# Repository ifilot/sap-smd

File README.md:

# Modular 8-bit "Simple as Possible" TTL-Logics Computer

This project showcases the design and construction of a modular 8-bit computer
built with TTL logic units. The core principle behind the project is to create a
**"Simple as Possible"** system, focusing on simplicity, modularity, and
compactness.

## Key Features

- **TTL Logic-Based Design**: The computer is built using traditional TTL
  (Transistor-Transistor Logic) components, adhering to a fundamental, hands-on
  approach to computing.
- **Modular Architecture**: Designed for modularity, each functional unit (ALU,
  registers, memory, control logic, etc.) is implemented as a separate module,
  allowing for easy debugging, customization, and scalability.
- **Compact Form Factor**: By predominantly using **SMD (Surface-Mount Device)**
  components, the overall size of the computer is significantly reduced compared
  to traditional through-hole designs, making it more efficient and portable.
- **Educational Value**: Serves as an excellent learning resource for
  understanding the basic principles of digital logic, computer architecture,
  and how these concepts come together to form a functional computing system.
- **Customization Potential**: The modular approach allows users to experiment
  with different configurations and expand the system to suit specific needs or
  projects.

## Technical specifications

- 8 bit program counter
- 256 bytes of RAM and 256 bytes of program ROM
- 256 configurable programs via a dip switch
- Three general-purpose register: A, B and T
- Simple ALU allowing for addition and subtraction
- EEPROM-configurable instruction decoder
- Custom assembly language including Python-based assembler

## Goals of the Project

The project aims to:
1. **Simplify Complexity**: Break down the workings of a computer into
   comprehensible modules without unnecessary abstraction.
2. **Promote Learning**: Provide an accessible platform for enthusiasts,
   educators, and students to explore computer design.
3. **Encourage Miniaturization**: Demonstrate how SMD components can be used
   effectively in hobbyist and educational projects to save space while
   maintaining functionality.

## Why SMD Components?

SMD components offer several advantages:
- **Space Efficiency**: Significantly smaller than through-hole components,
  enabling more compact designs.
- **Modern Availability**: Easier to source and more reflective of contemporary
  electronics practices.
- **Scalability**: Allows for a more complex system without requiring excessive
  physical space.

## Who Is This For?

This project is ideal for:
- **Hobbyists and Makers** interested in retrocomputing and hardware design.
- **Students and Educators** looking for hands-on experience with digital logic
  and computing fundamentals.
- **Researchers and Enthusiasts** exploring minimalist computing and modular
  design approaches.

## Getting Started

1. **Clone the Repository**: Download the files and schematics from this
   repository.
2. **Review the Documentation**: Detailed explanations and schematics for each
   module are available in the `docs` directory.
3. **Assemble and Test**: Follow the provided instructions to assemble and test
   the modules step-by-step.
4. **Customize**: Modify or expand the design to suit your needs or explore
   specific areas of interest.

## Contributing

Contributions to this project are welcome! If you have ideas for improvements,
additional features, or alternative designs, feel free to fork the repository
and submit a pull request.

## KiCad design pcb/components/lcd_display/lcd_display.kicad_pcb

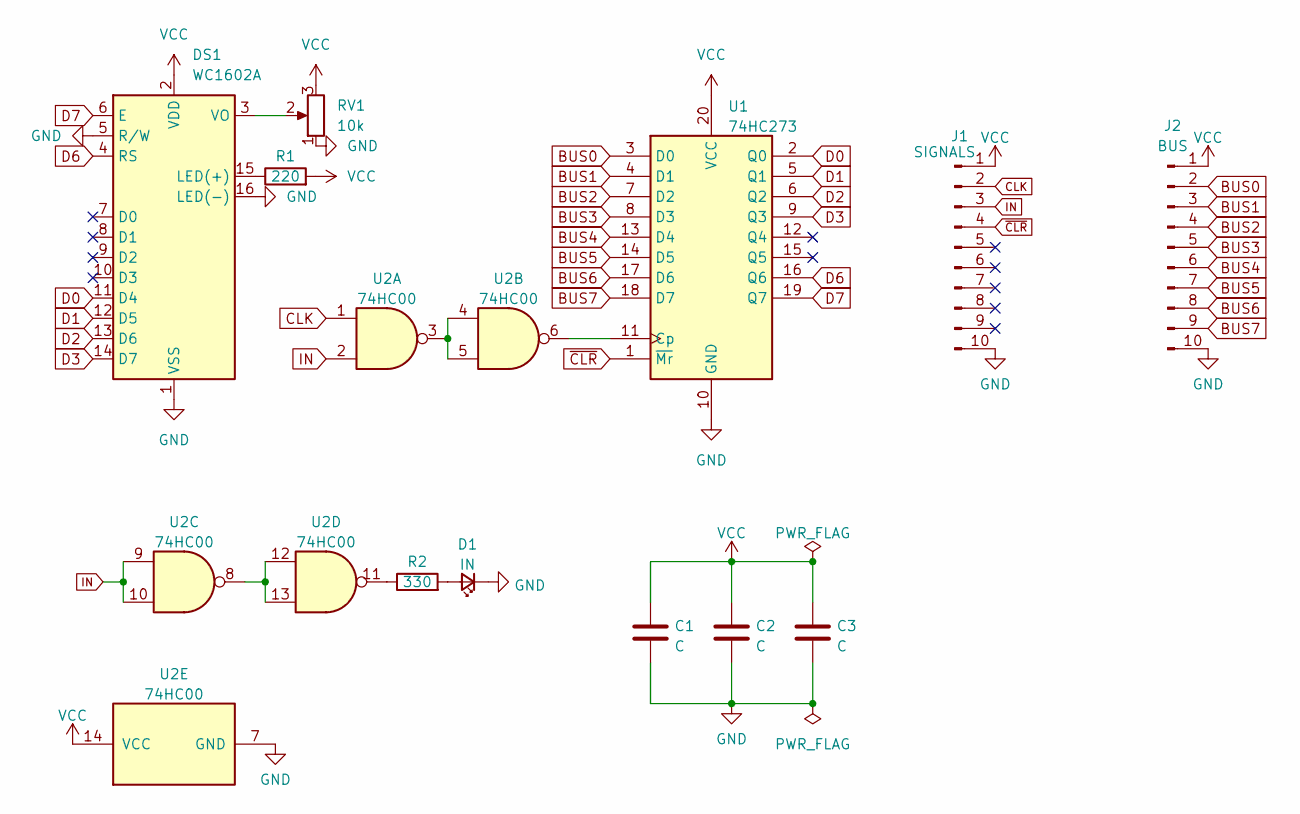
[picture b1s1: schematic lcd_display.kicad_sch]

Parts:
C1, C2, C3: C; C_0805_2012Metric
D1: IN; LED_0805_2012Metric
DS1: WC1602A
J1: SIGNALS; PinHeader_1x10_P2.54mm_Vertical
J2: BUS; PinHeader_1x10_P2.54mm_Vertical
R1: 220; R_0805_2012Metric
R2: 330; R_0805_2012Metric
RV1: 10k; Potentiometer_Bourns_3296W_Vertical
U1: 74HC273; SOIC-20W_7.5x12.8mm_P1.27mm
U2: 74HC00; SO-14_3.9x8.65mm_P1.27mm

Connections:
BUS0: J2.2, U1.3 (D0)
BUS1: J2.3, U1.4 (D1)
BUS2: J2.4, U1.7 (D2)
BUS3: J2.5, U1.8 (D3)
BUS4: J2.6, U1.13 (D4)
BUS5: J2.7, U1.14 (D5)
BUS6: J2.8, U1.17 (D6)
BUS7: J2.9, U1.18 (D7)
CLK: J1.2, U2.1
D0: DS1.11 (D4), U1.2 (Q0)
D1: DS1.12 (D5), U1.5 (Q1)
D2: DS1.13 (D6), U1.6 (Q2)
D3: DS1.14 (D7), U1.9 (Q3)
D6: DS1.4 (RS), U1.16 (Q6)
D7: DS1.6 (E), U1.19 (Q7)
GND: C1.2, C2.2, C3.2, D1.1 (K), DS1.1 (VSS), DS1.5 (R/W), DS1.16 (LED(-)), J1.10, J2.10, RV1.1, U1.10 (GND), U2.7 (GND)
IN: J1.3, U2.2, U2.9, U2.10
unnamed: D1.2 (A), R2.2
unnamed: DS1.15 (LED(+)), R1.1
unnamed: DS1.3 (VO), RV1.2
unnamed: R2.1, U2.11
unnamed: U1.11 (Cp), U2.6
unnamed: U2.3, U2.4, U2.5
unnamed: U2.8, U2.12, U2.13
VCC: C1.1, C2.1, C3.1, DS1.2 (VDD), J1.1, J2.1, R1.2, RV1.3, U1.20 (VCC), U2.14 (VCC)
~CLR: J1.4, U1.1 (~Mr)

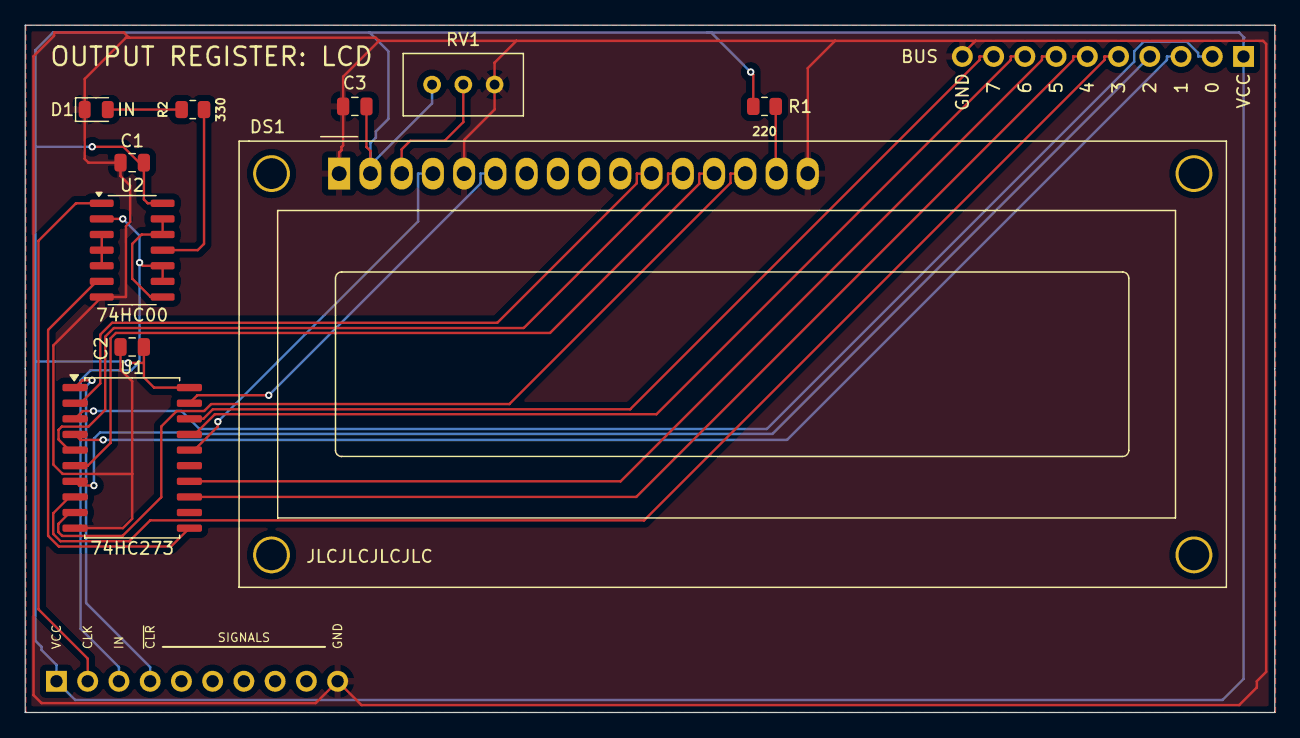
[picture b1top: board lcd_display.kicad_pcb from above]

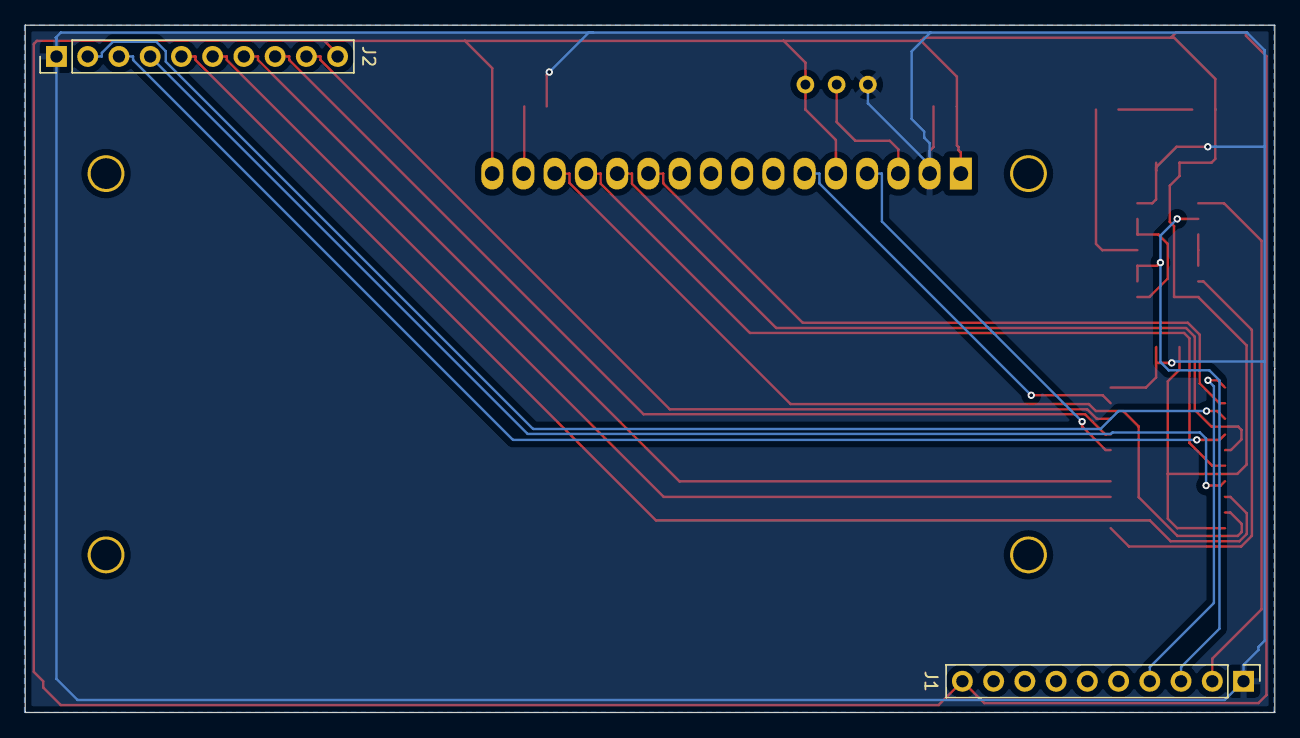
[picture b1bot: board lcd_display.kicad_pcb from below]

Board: 2 copper layers, 101.6 x 55.9 mm, 12 parts (2 on the bottom side), 26 nets.

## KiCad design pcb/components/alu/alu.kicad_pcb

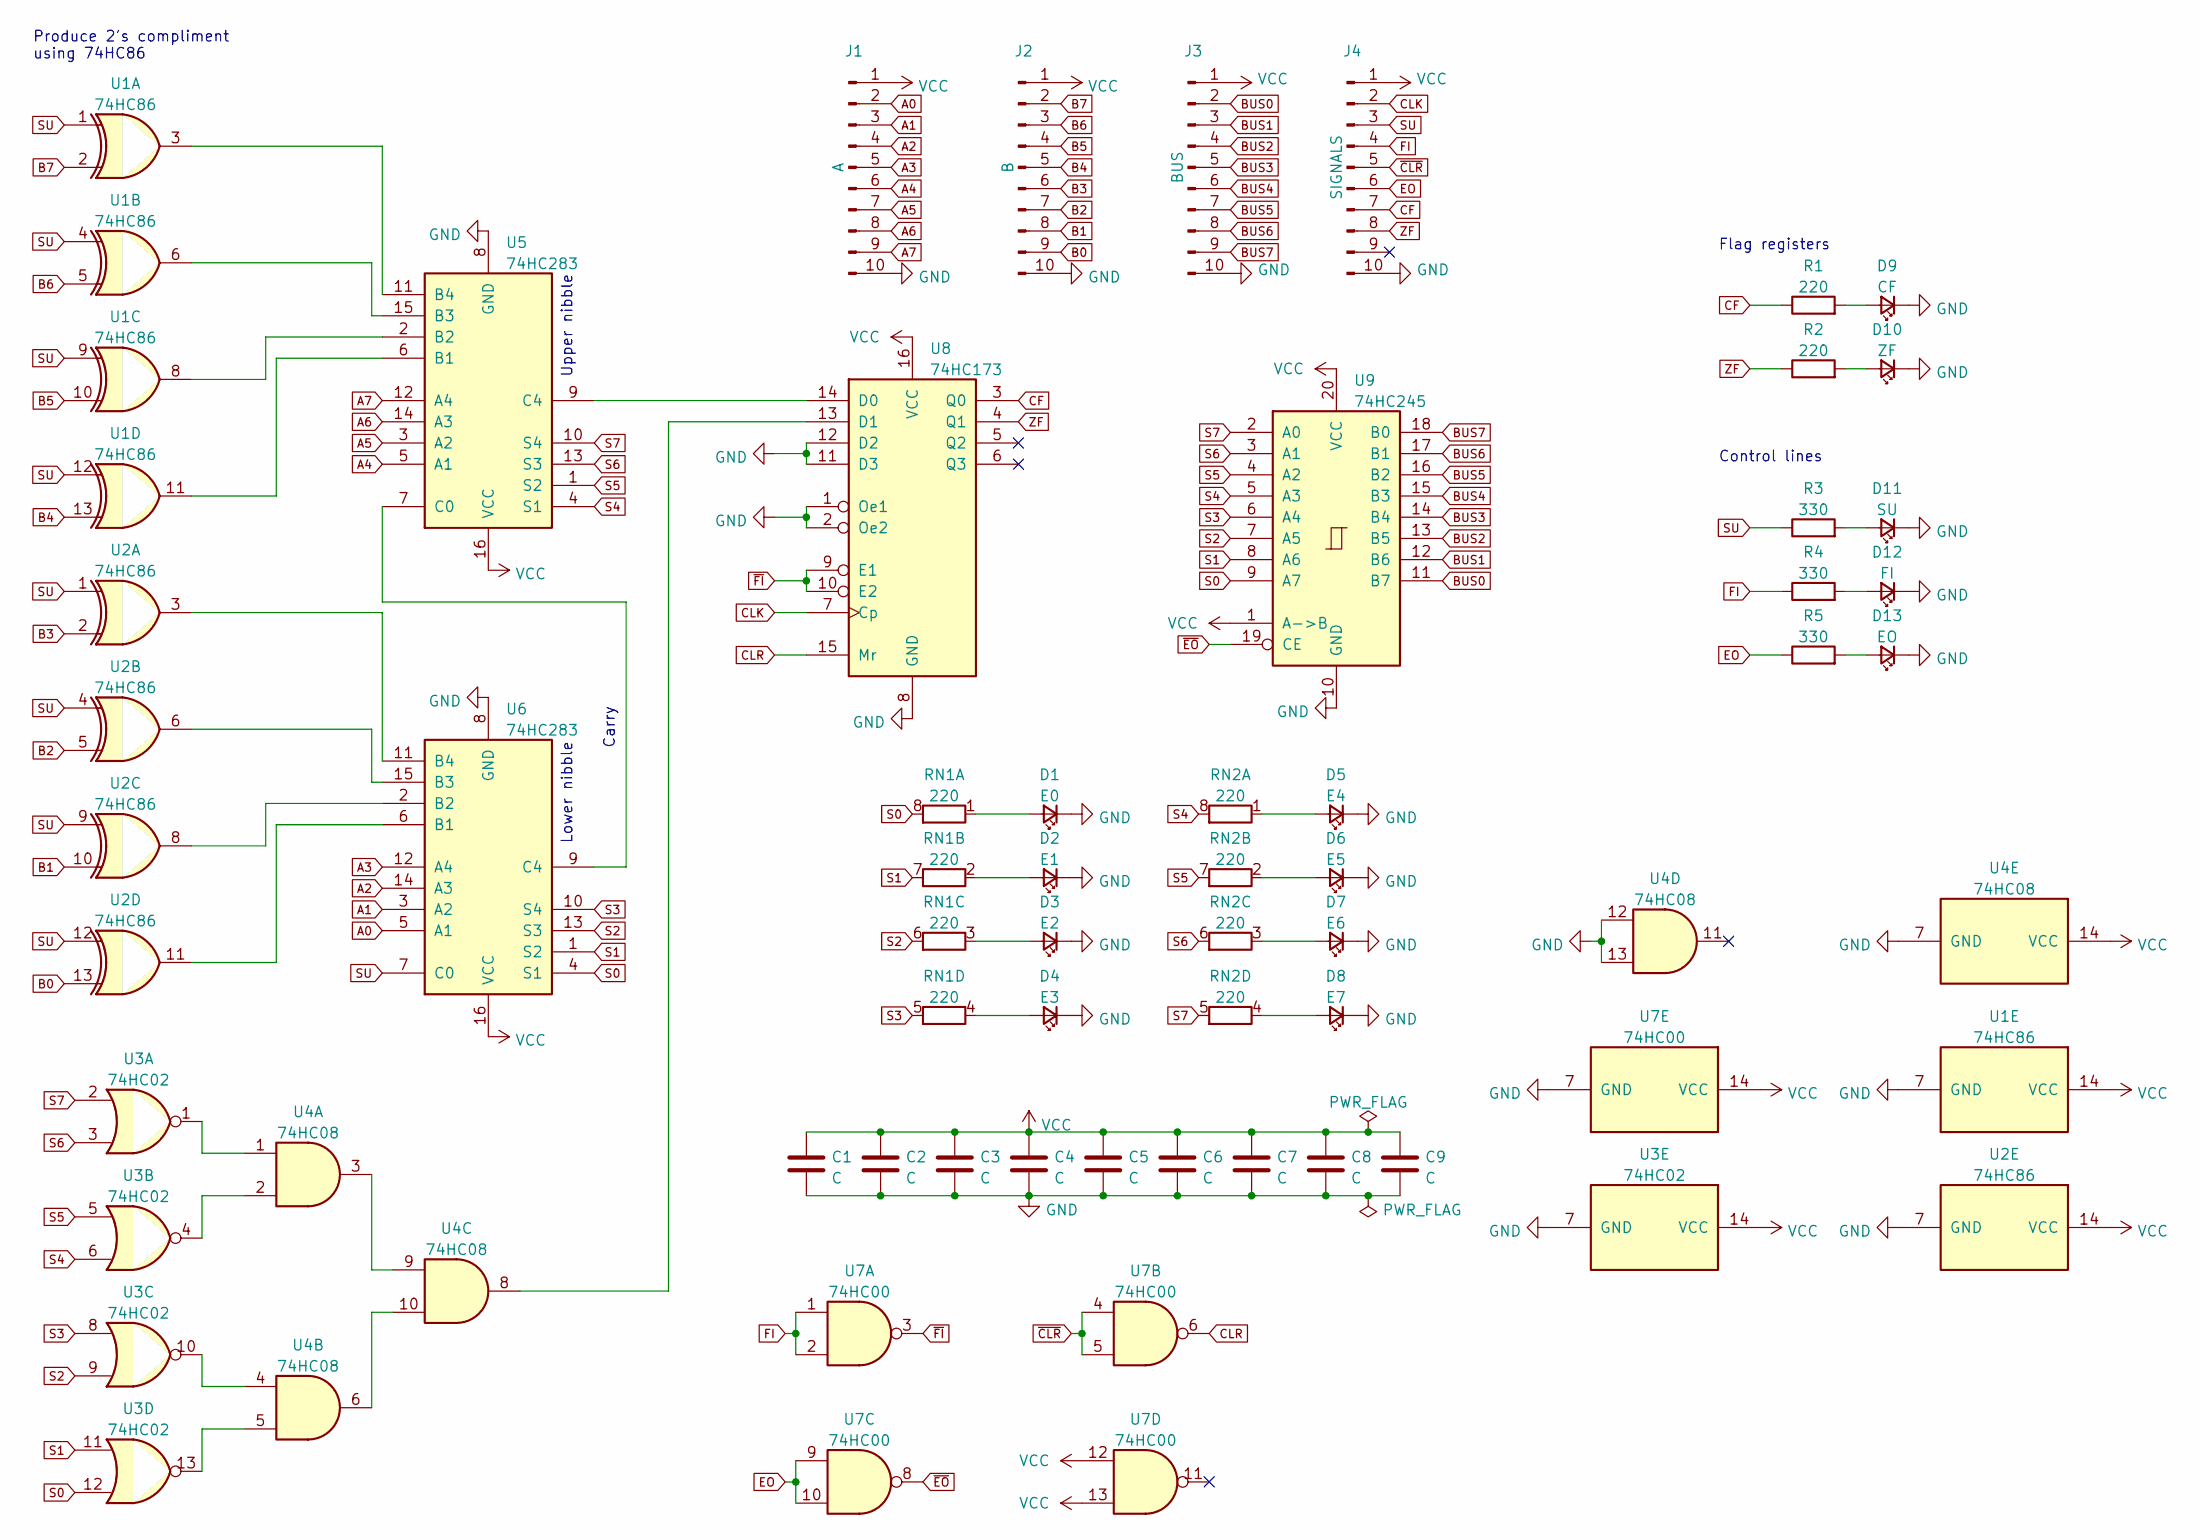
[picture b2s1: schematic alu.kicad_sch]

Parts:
C1, C2, C3, C4, C5, C6, C7, C8, C9: C; C_0805_2012Metric
D1: E0; LED_0805_2012Metric
D2: E1; LED_0805_2012Metric
D3: E2; LED_0805_2012Metric
D4: E3; LED_0805_2012Metric
D5: E4; LED_0805_2012Metric
D6: E5; LED_0805_2012Metric
D7: E6; LED_0805_2012Metric
D8: E7; LED_0805_2012Metric
D9: CF; LED_0805_2012Metric
D10: ZF; LED_0805_2012Metric
D11: SU; LED_0805_2012Metric
D12: FI; LED_0805_2012Metric
D13: EO; LED_0805_2012Metric
J1: A; PinHeader_1x10_P2.54mm_Vertical
J2: B; PinHeader_1x10_P2.54mm_Vertical
J3: BUS; PinHeader_1x10_P2.54mm_Vertical
J4: SIGNALS; PinHeader_1x10_P2.54mm_Vertical
R1, R2: 220; R_0805_2012Metric
R3, R4, R5: 330; R_0805_2012Metric
RN1, RN2: 220; R_Array_Convex_4x0603
U1, U2: 74HC86; SO-14_3.9x8.65mm_P1.27mm
U3: 74HC02; SO-14_3.9x8.65mm_P1.27mm
U4: 74HC08; SO-14_3.9x8.65mm_P1.27mm
U5, U6: 74HC283; SO-16_3.9x9.9mm_P1.27mm
U7: 74HC00; SO-14_3.9x8.65mm_P1.27mm
U8: 74HC173; SO-16_3.9x9.9mm_P1.27mm
U9: 74HC245; SO-20_12.8x7.5mm_P1.27mm

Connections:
A0: J1.2, U6.5 (A1)
A1: J1.3, U6.3 (A2)
A2: J1.4, U6.14 (A3)
A3: J1.5, U6.12 (A4)
A4: J1.6, U5.5 (A1)
A5: J1.7, U5.3 (A2)
A6: J1.8, U5.14 (A3)
A7: J1.9, U5.12 (A4)
B0: J2.9, U2.13
B1: J2.8, U2.10
B2: J2.7, U2.5
B3: J2.6, U2.2
B4: J2.5, U1.13
B5: J2.4, U1.10
B6: J2.3, U1.5
B7: J2.2, U1.2
BUS0: J3.2, U9.11 (B7)
BUS1: J3.3, U9.12 (B6)
BUS2: J3.4, U9.13 (B5)
BUS3: J3.5, U9.14 (B4)
BUS4: J3.6, U9.15 (B3)
BUS5: J3.7, U9.16 (B2)
BUS6: J3.8, U9.17 (B1)
BUS7: J3.9, U9.18 (B0)
CF: J4.7, R1.1, U8.3 (Q0)
CLK: J4.2, U8.7 (Cp)
CLR: U7.6, U8.15 (Mr)
EO: J4.6, R5.1, U7.9, U7.10
FI: J4.4, R4.1, U7.1, U7.2
GND: C1.2, C2.2, C3.2, C4.2, C5.2, C6.2, C7.2, C8.2, C9.2, D1.1 (K), D2.1 (K), D3.1 (K), D4.1 (K), D5.1 (K), D6.1 (K), D7.1 (K), D8.1 (K), D9.1 (K), D10.1 (K), D11.1 (K), D12.1 (K), D13.1 (K), J1.10, J2.10, J3.10, J4.10, U1.7 (GND), U2.7 (GND), U3.7 (GND), U4.7 (GND), U4.12, U4.13, U5.8 (GND), U6.8 (GND), U7.7 (GND), U8.1 (Oe1), U8.2 (Oe2), U8.8 (GND), U8.11 (D3), U8.12 (D2), U9.10 (GND)
unnamed: D1.2 (A), RN1.1 (R1.1)
unnamed: D2.2 (A), RN1.2 (R2.1)
unnamed: D3.2 (A), RN1.3 (R3.1)
unnamed: D4.2 (A), RN1.4 (R4.1)
unnamed: D5.2 (A), RN2.1 (R1.1)
unnamed: D6.2 (A), RN2.2 (R2.1)
unnamed: D7.2 (A), RN2.3 (R3.1)
unnamed: D8.2 (A), RN2.4 (R4.1)
unnamed: D9.2 (A), R1.2
unnamed: D10.2 (A), R2.2
unnamed: D11.2 (A), R3.2
unnamed: D12.2 (A), R4.2
unnamed: D13.2 (A), R5.2
unnamed: U1.3, U5.11 (B4)
unnamed: U1.6, U5.15 (B3)
unnamed: U1.8, U5.2 (B2)
unnamed: U1.11, U5.6 (B1)
unnamed: U2.3, U6.11 (B4)
unnamed: U2.6, U6.15 (B3)
unnamed: U2.8, U6.2 (B2)
unnamed: U2.11, U6.6 (B1)
unnamed: U3.1, U4.1
unnamed: U3.4, U4.2
unnamed: U3.10, U4.4
unnamed: U3.13, U4.5
unnamed: U4.3, U4.9
unnamed: U4.8, U8.13 (D1)
unnamed: U4.6, U4.10
unnamed: U5.7 (C0), U6.9 (C4)
unnamed: U5.9 (C4), U8.14 (D0)
S0: RN1.8 (R1.2), U3.12, U6.4 (S1), U9.9 (A7)
S1: RN1.7 (R2.2), U3.11, U6.1 (S2), U9.8 (A6)
S2: RN1.6 (R3.2), U3.9, U6.13 (S3), U9.7 (A5)
S3: RN1.5 (R4.2), U3.8, U6.10 (S4), U9.6 (A4)
S4: RN2.8 (R1.2), U3.6, U5.4 (S1), U9.5 (A3)
S5: RN2.7 (R2.2), U3.5, U5.1 (S2), U9.4 (A2)
S6: RN2.6 (R3.2), U3.3, U5.13 (S3), U9.3 (A1)
S7: RN2.5 (R4.2), U3.2, U5.10 (S4), U9.2 (A0)
SU: J4.3, R3.1, U1.1, U1.4, U1.9, U1.12, U2.1, U2.4, U2.9, U2.12, U6.7 (C0)
VCC: C1.1, C2.1, C3.1, C4.1, C5.1, C6.1, C7.1, C8.1, C9.1, J1.1, J2.1, J3.1, J4.1, U1.14 (VCC), U2.14 (VCC), U3.14 (VCC), U4.14 (VCC), U5.16 (VCC), U6.16 (VCC), U7.12, U7.13, U7.14 (VCC), U8.16 (VCC), U9.1 (A->B), U9.20 (VCC)
ZF: J4.8, R2.1, U8.4 (Q1)
~CLR: J4.5, U7.4, U7.5
~EO: U7.8, U9.19 (CE)
~FI: U7.3, U8.9 (E1), U8.10 (E2)

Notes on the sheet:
Produce 2's compliment using 74HC86
Control lines
Flag registers
Upper nibble
Carry
Lower nibble

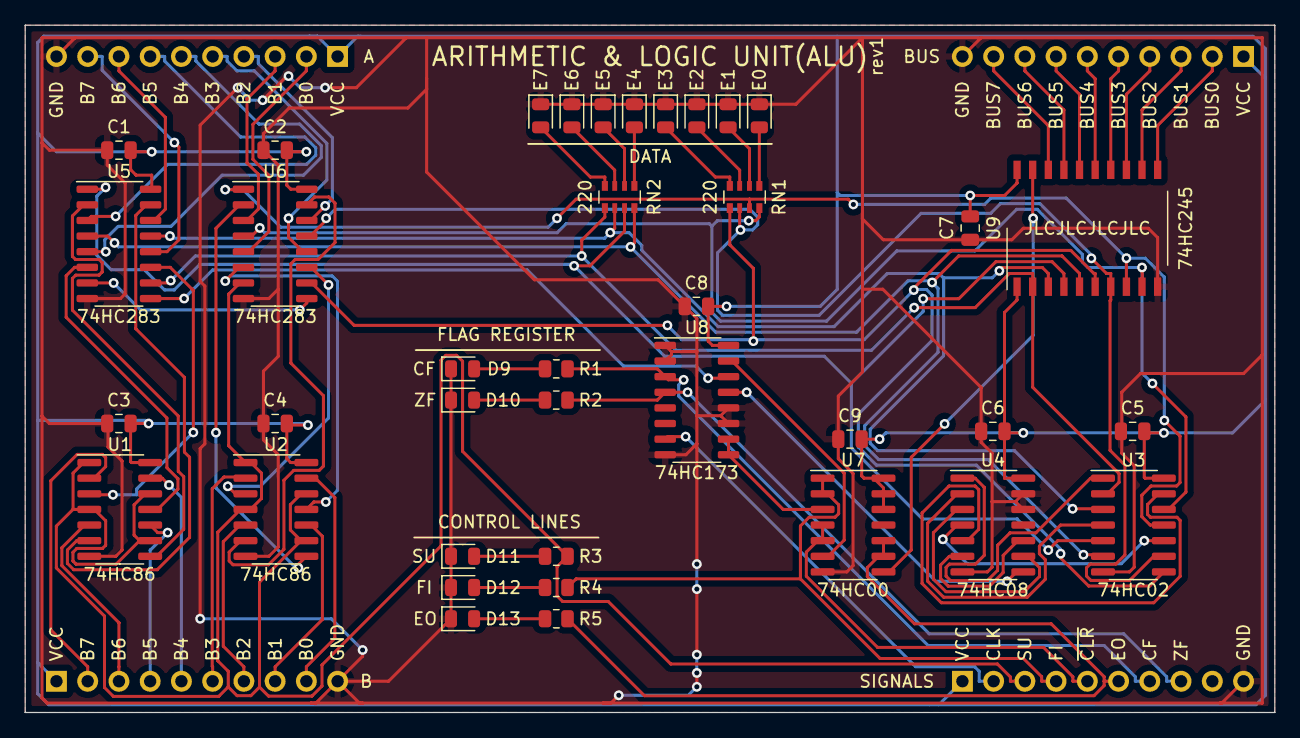
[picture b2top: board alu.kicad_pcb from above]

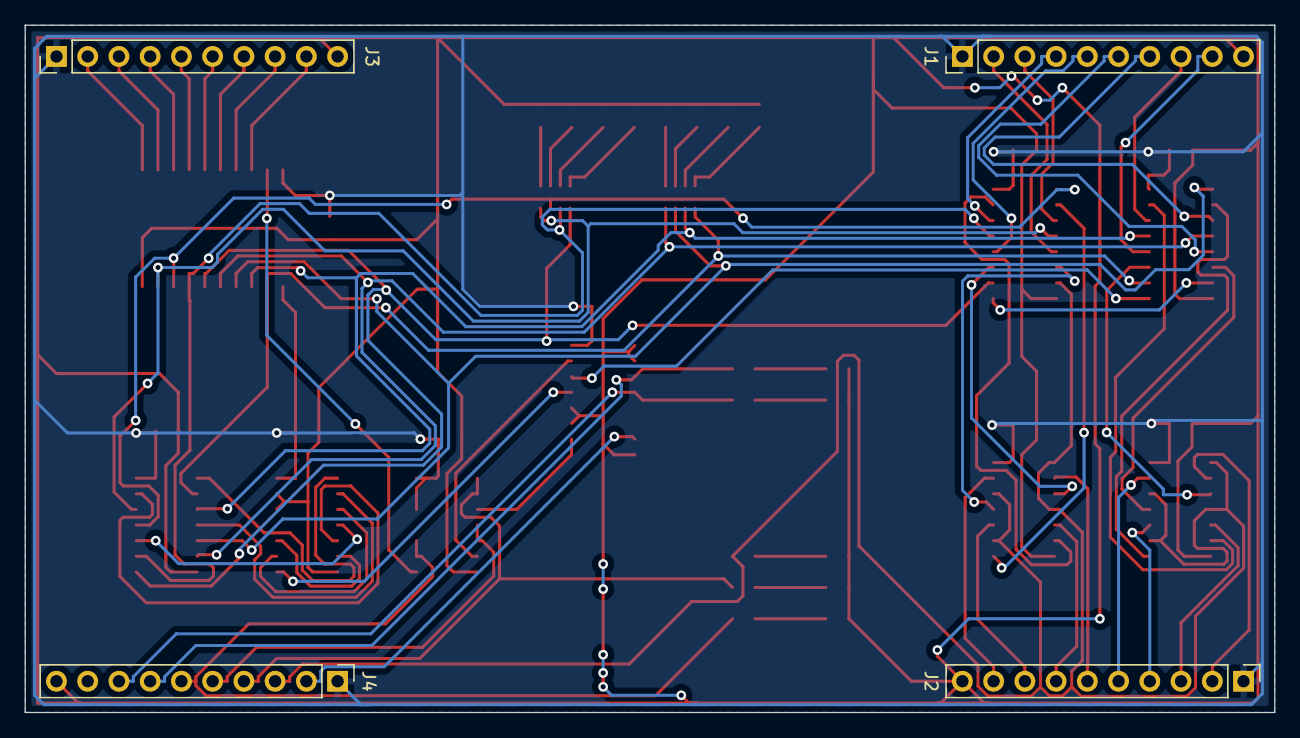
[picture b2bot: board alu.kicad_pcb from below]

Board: 2 copper layers, 101.6 x 55.9 mm, 42 parts (4 on the bottom side), 74 nets.

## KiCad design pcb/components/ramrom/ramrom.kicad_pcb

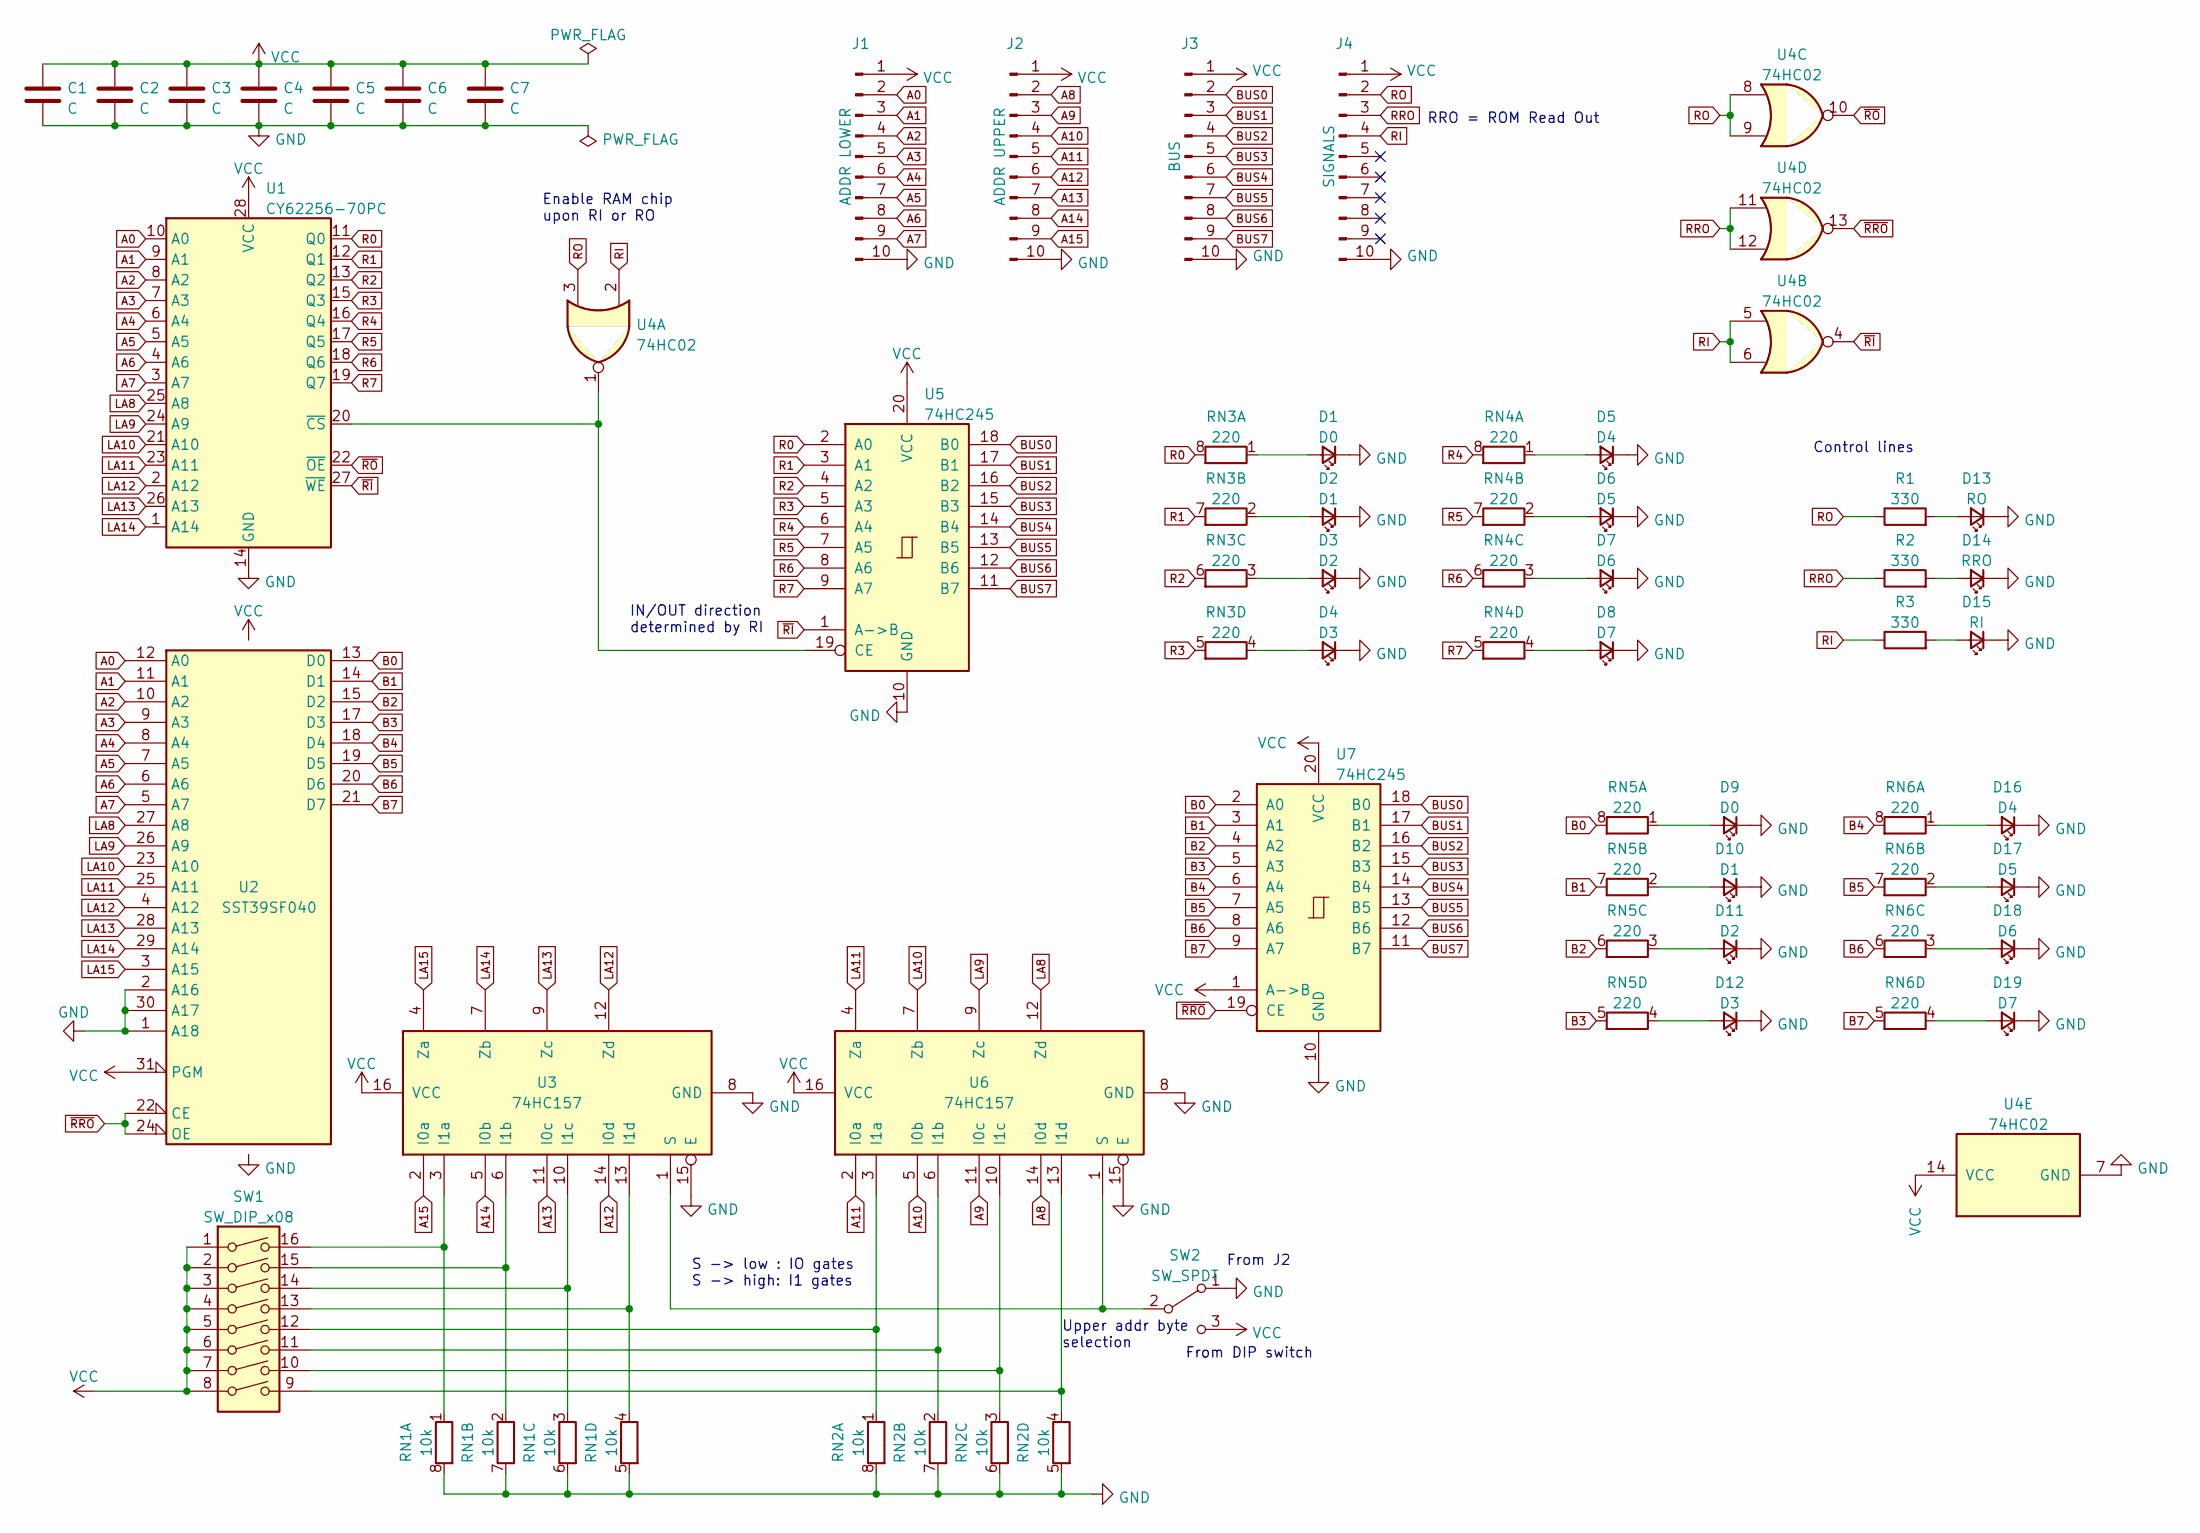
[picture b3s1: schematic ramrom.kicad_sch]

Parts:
C1, C2, C3, C4, C5, C6, C7: C; C_0805_2012Metric
D1, D9: D0; LED_0805_2012Metric
D2, D10: D1; LED_0805_2012Metric
D3, D11: D2; LED_0805_2012Metric
D4, D12: D3; LED_0805_2012Metric
D5, D16: D4; LED_0805_2012Metric
D6, D17: D5; LED_0805_2012Metric
D7, D18: D6; LED_0805_2012Metric
D8, D19: D7; LED_0805_2012Metric
D13: RO; LED_0805_2012Metric
D14: RRO; LED_0805_2012Metric
D15: RI; LED_0805_2012Metric
J1: ADDR LOWER; PinHeader_1x10_P2.54mm_Vertical
J2: ADDR UPPER; PinHeader_1x10_P2.54mm_Vertical
J3: BUS; PinHeader_1x10_P2.54mm_Vertical
J4: SIGNALS; PinHeader_1x10_P2.54mm_Vertical
R1, R2, R3: 330; R_0805_2012Metric
RN1, RN2: 10k; R_Array_Convex_4x0603
RN3, RN4, RN5, RN6: 220; R_Array_Convex_4x0603
SW1: SW_DIP_x08; SW_DIP_SPSTx08_Slide_6.7x21.88mm_W7.62mm_P2.54mm_LowProfile
SW2: SW_SPDT; SW_Slide_1P2T_CK_OS102011MS2Q
U1: CY62256-70PC; DIP-28_W15.24mm_Socket
U2: SST39SF040; DIP-32_W15.24mm_Socket
U3, U6: 74HC157; SO-16_3.9x9.9mm_P1.27mm
U4: 74HC02; SO-14_3.9x8.65mm_P1.27mm
U5, U7: 74HC245; SO-20_12.8x7.5mm_P1.27mm

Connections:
A0: J1.2, U1.10 (A0), U2.12 (A0)
A1: J1.3, U1.9 (A1), U2.11 (A1)
A2: J1.4, U1.8 (A2), U2.10 (A2)
A3: J1.5, U1.7 (A3), U2.9 (A3)
A4: J1.6, U1.6 (A4), U2.8 (A4)
A5: J1.7, U1.5 (A5), U2.7 (A5)
A6: J1.8, U1.4 (A6), U2.6 (A6)
A7: J1.9, U1.3 (A7), U2.5 (A7)
A8: J2.2, U6.14 (I0d)
A9: J2.3, U6.11 (I0c)
A10: J2.4, U6.5 (I0b)
A11: J2.5, U6.2 (I0a)
A12: J2.6, U3.14 (I0d)
A13: J2.7, U3.11 (I0c)
A14: J2.8, U3.5 (I0b)
A15: J2.9, U3.2 (I0a)
B0: RN5.8 (R1.2), U2.13 (D0), U7.2 (A0)
B1: RN5.7 (R2.2), U2.14 (D1), U7.3 (A1)
B2: RN5.6 (R3.2), U2.15 (D2), U7.4 (A2)
B3: RN5.5 (R4.2), U2.17 (D3), U7.5 (A3)
B4: RN6.8 (R1.2), U2.18 (D4), U7.6 (A4)
B5: RN6.7 (R2.2), U2.19 (D5), U7.7 (A5)
B6: RN6.6 (R3.2), U2.20 (D6), U7.8 (A6)
B7: RN6.5 (R4.2), U2.21 (D7), U7.9 (A7)
BUS0: J3.2, U5.18 (B0), U7.18 (B0)
BUS1: J3.3, U5.17 (B1), U7.17 (B1)
BUS2: J3.4, U5.16 (B2), U7.16 (B2)
BUS3: J3.5, U5.15 (B3), U7.15 (B3)
BUS4: J3.6, U5.14 (B4), U7.14 (B4)
BUS5: J3.7, U5.13 (B5), U7.13 (B5)
BUS6: J3.8, U5.12 (B6), U7.12 (B6)
BUS7: J3.9, U5.11 (B7), U7.11 (B7)
GND: C1.2, C2.2, C3.2, C4.2, C5.2, C6.2, C7.2, D1.1 (K), D2.1 (K), D3.1 (K), D4.1 (K), D5.1 (K), D6.1 (K), D7.1 (K), D8.1 (K), D9.1 (K), D10.1 (K), D11.1 (K), D12.1 (K), D13.1 (K), D14.1 (K), D15.1 (K), D16.1 (K), D17.1 (K), D18.1 (K), D19.1 (K), J1.10, J2.10, J3.10, J4.10, RN1.5 (R4.2), RN1.6 (R3.2), RN1.7 (R2.2), RN1.8 (R1.2), RN2.5 (R4.2), RN2.6 (R3.2), RN2.7 (R2.2), RN2.8 (R1.2), SW2.1 (A), U1.14 (GND), U2.1 (A18), U2.2 (A16), U2.16 (GND), U2.30 (A17), U3.8 (GND), U3.15 (E), U4.7 (GND), U5.10 (GND), U6.8 (GND), U6.15 (E), U7.10 (GND)
LA8: U1.25 (A8), U2.27 (A8), U6.12 (Zd)
LA9: U1.24 (A9), U2.26 (A9), U6.9 (Zc)
LA10: U1.21 (A10), U2.23 (A10), U6.7 (Zb)
LA11: U1.23 (A11), U2.25 (A11), U6.4 (Za)
LA12: U1.2 (A12), U2.4 (A12), U3.12 (Zd)
LA13: U1.26 (A13), U2.28 (A13), U3.9 (Zc)
LA14: U1.1 (A14), U2.29 (A14), U3.7 (Zb)
LA15: U2.3 (A15), U3.4 (Za)
unnamed: D1.2 (A), RN3.1 (R1.1)
unnamed: D2.2 (A), RN3.2 (R2.1)
unnamed: D3.2 (A), RN3.3 (R3.1)
unnamed: D4.2 (A), RN3.4 (R4.1)
unnamed: D5.2 (A), RN4.1 (R1.1)
unnamed: D6.2 (A), RN4.2 (R2.1)
unnamed: D7.2 (A), RN4.3 (R3.1)
unnamed: D8.2 (A), RN4.4 (R4.1)
unnamed: D9.2 (A), RN5.1 (R1.1)
unnamed: D10.2 (A), RN5.2 (R2.1)
unnamed: D11.2 (A), RN5.3 (R3.1)
unnamed: D12.2 (A), RN5.4 (R4.1)
unnamed: D13.2 (A), R1.2
unnamed: D14.2 (A), R2.2
unnamed: D15.2 (A), R3.2
unnamed: D16.2 (A), RN6.1 (R1.1)
unnamed: D17.2 (A), RN6.2 (R2.1)
unnamed: D18.2 (A), RN6.3 (R3.1)
unnamed: D19.2 (A), RN6.4 (R4.1)
unnamed: RN1.1 (R1.1), SW1.16, U3.3 (I1a)
unnamed: RN1.2 (R2.1), SW1.15, U3.6 (I1b)
unnamed: RN1.3 (R3.1), SW1.14, U3.10 (I1c)
unnamed: RN1.4 (R4.1), SW1.13, U3.13 (I1d)
unnamed: RN2.1 (R1.1), SW1.12, U6.3 (I1a)
unnamed: RN2.2 (R2.1), SW1.11, U6.6 (I1b)
unnamed: RN2.3 (R3.1), SW1.10, U6.10 (I1c)
unnamed: RN2.4 (R4.1), SW1.9, U6.13 (I1d)
unnamed: SW2.2 (B), U3.1 (S), U6.1 (S)
unnamed: U1.20 (~CS), U4.1, U5.19 (CE)
R0: RN3.8 (R1.2), U1.11 (Q0), U5.2 (A0)
R1: RN3.7 (R2.2), U1.12 (Q1), U5.3 (A1)
R2: RN3.6 (R3.2), U1.13 (Q2), U5.4 (A2)
R3: RN3.5 (R4.2), U1.15 (Q3), U5.5 (A3)
R4: RN4.8 (R1.2), U1.16 (Q4), U5.6 (A4)
R5: RN4.7 (R2.2), U1.17 (Q5), U5.7 (A5)
R6: RN4.6 (R3.2), U1.18 (Q6), U5.8 (A6)
R7: RN4.5 (R4.2), U1.19 (Q7), U5.9 (A7)
RI: J4.4, R3.1, U4.2, U4.5, U4.6
RO: J4.2, R1.1, U4.3, U4.8, U4.9
RRO: J4.3, R2.1, U4.11, U4.12
VCC: C1.1, C2.1, C3.1, C4.1, C5.1, C6.1, C7.1, J1.1, J2.1, J3.1, J4.1, SW1.1, SW1.2, SW1.3, SW1.4, SW1.5, SW1.6, SW1.7, SW1.8, SW2.3 (C), U1.28 (VCC), U2.31 (PGM), U2.32 (VCC), U3.16 (VCC), U4.14 (VCC), U5.20 (VCC), U6.16 (VCC), U7.1 (A->B), U7.20 (VCC)
~RI: U1.27 (~WE), U4.4, U5.1 (A->B)
~RO: U1.22 (~OE), U4.10
~RRO: U2.22 (CE), U2.24 (OE), U4.13, U7.19 (CE)

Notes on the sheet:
Upper addr byte selection
From J2
Control lines
From DIP switch
Enable RAM chip upon RI or RO
S -> low : IO gates S -> high: I1 gates
IN/OUT direction determined by RI
RRO = ROM Read Out

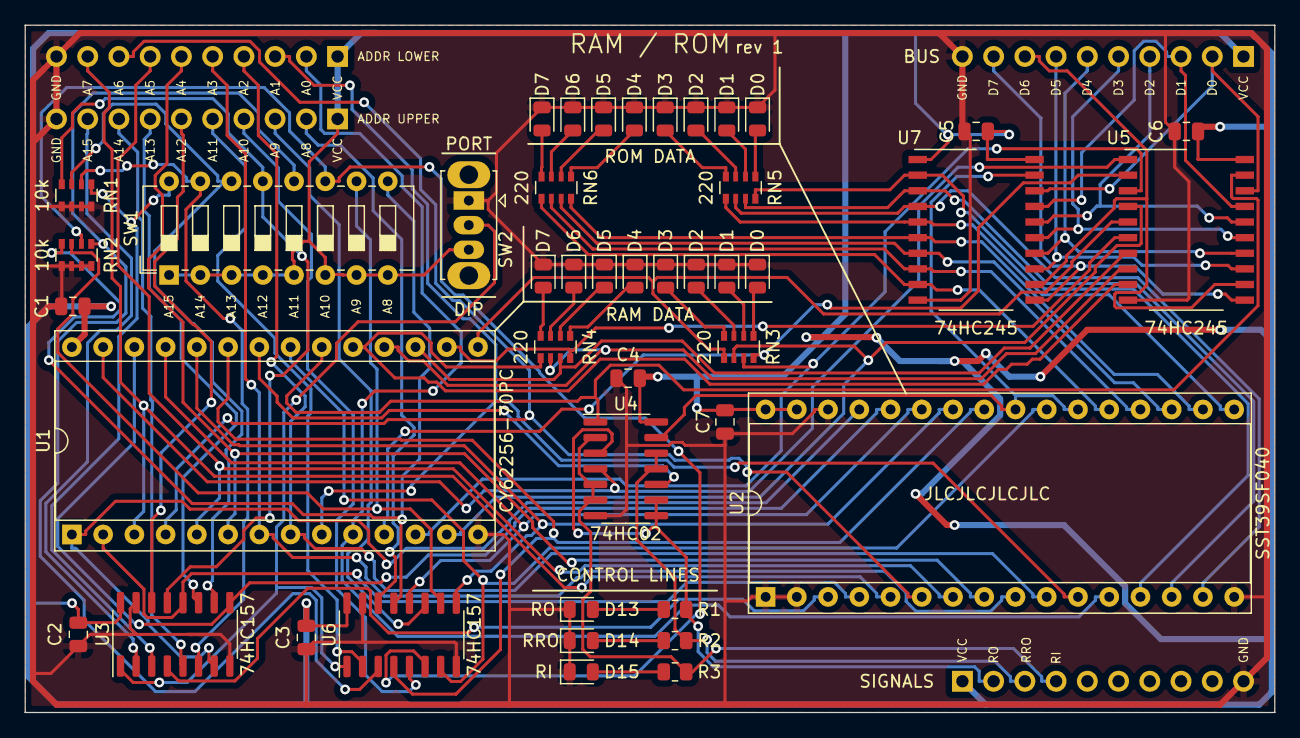
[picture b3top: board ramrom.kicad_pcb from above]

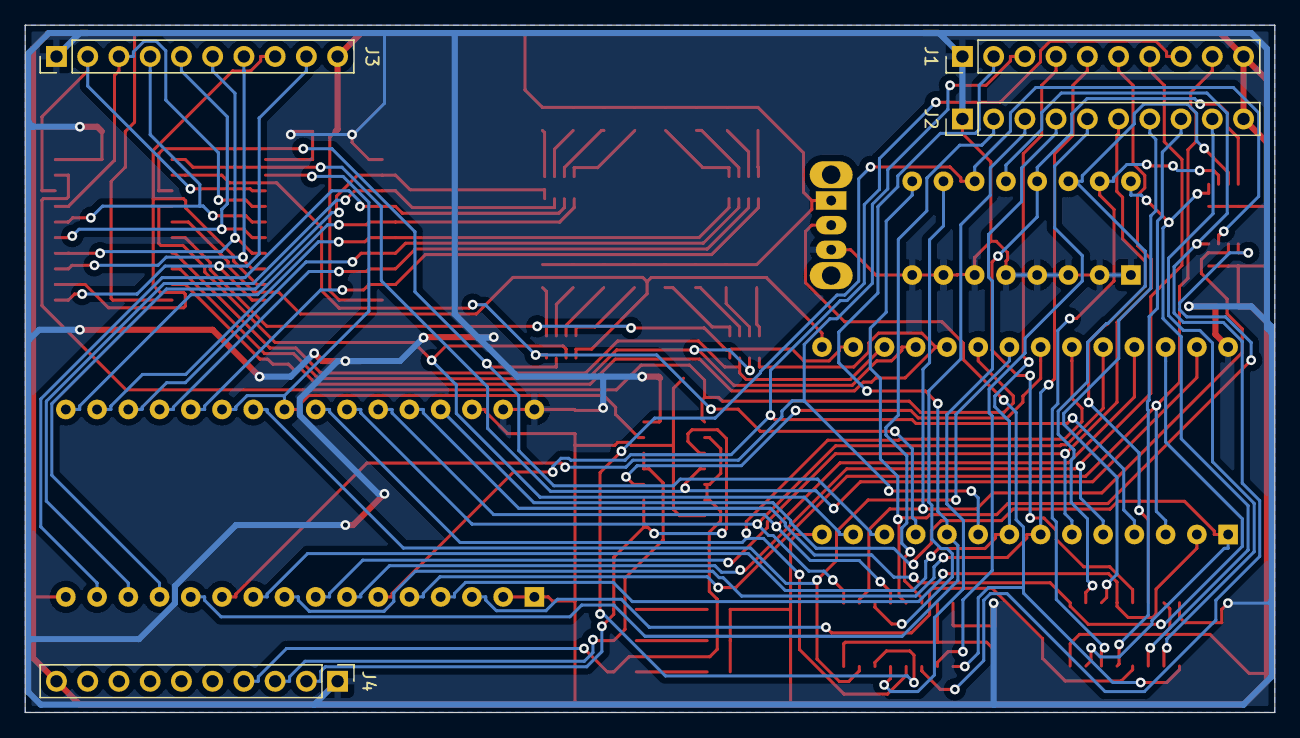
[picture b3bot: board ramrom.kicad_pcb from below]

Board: 2 copper layers, 101.6 x 55.9 mm, 48 parts (4 on the bottom side), 85 nets.

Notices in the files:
README.md:
CERN-OHL
